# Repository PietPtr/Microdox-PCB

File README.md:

# Microdox-PCB
PCB for the Microdox keyboard.

## License

Copyright (c) 2016 Pieter Staal

This design is free software: you can redistribute it and/or modify
it under the terms of the GNU General Public License as published by
the Free Software Foundation, either version 3 of the License, or
(at your option) any later version.

This design is distributed in the hope that it will be useful,
but WITHOUT ANY WARRANTY; without even the implied warranty of
MERCHANTABILITY or FITNESS FOR A PARTICULAR PURPOSE.  See the
GNU General Public License for more details.

You should have received a copy of the GNU General Public License
along with this design.  If not, see <http://www.gnu.org/licenses/>.

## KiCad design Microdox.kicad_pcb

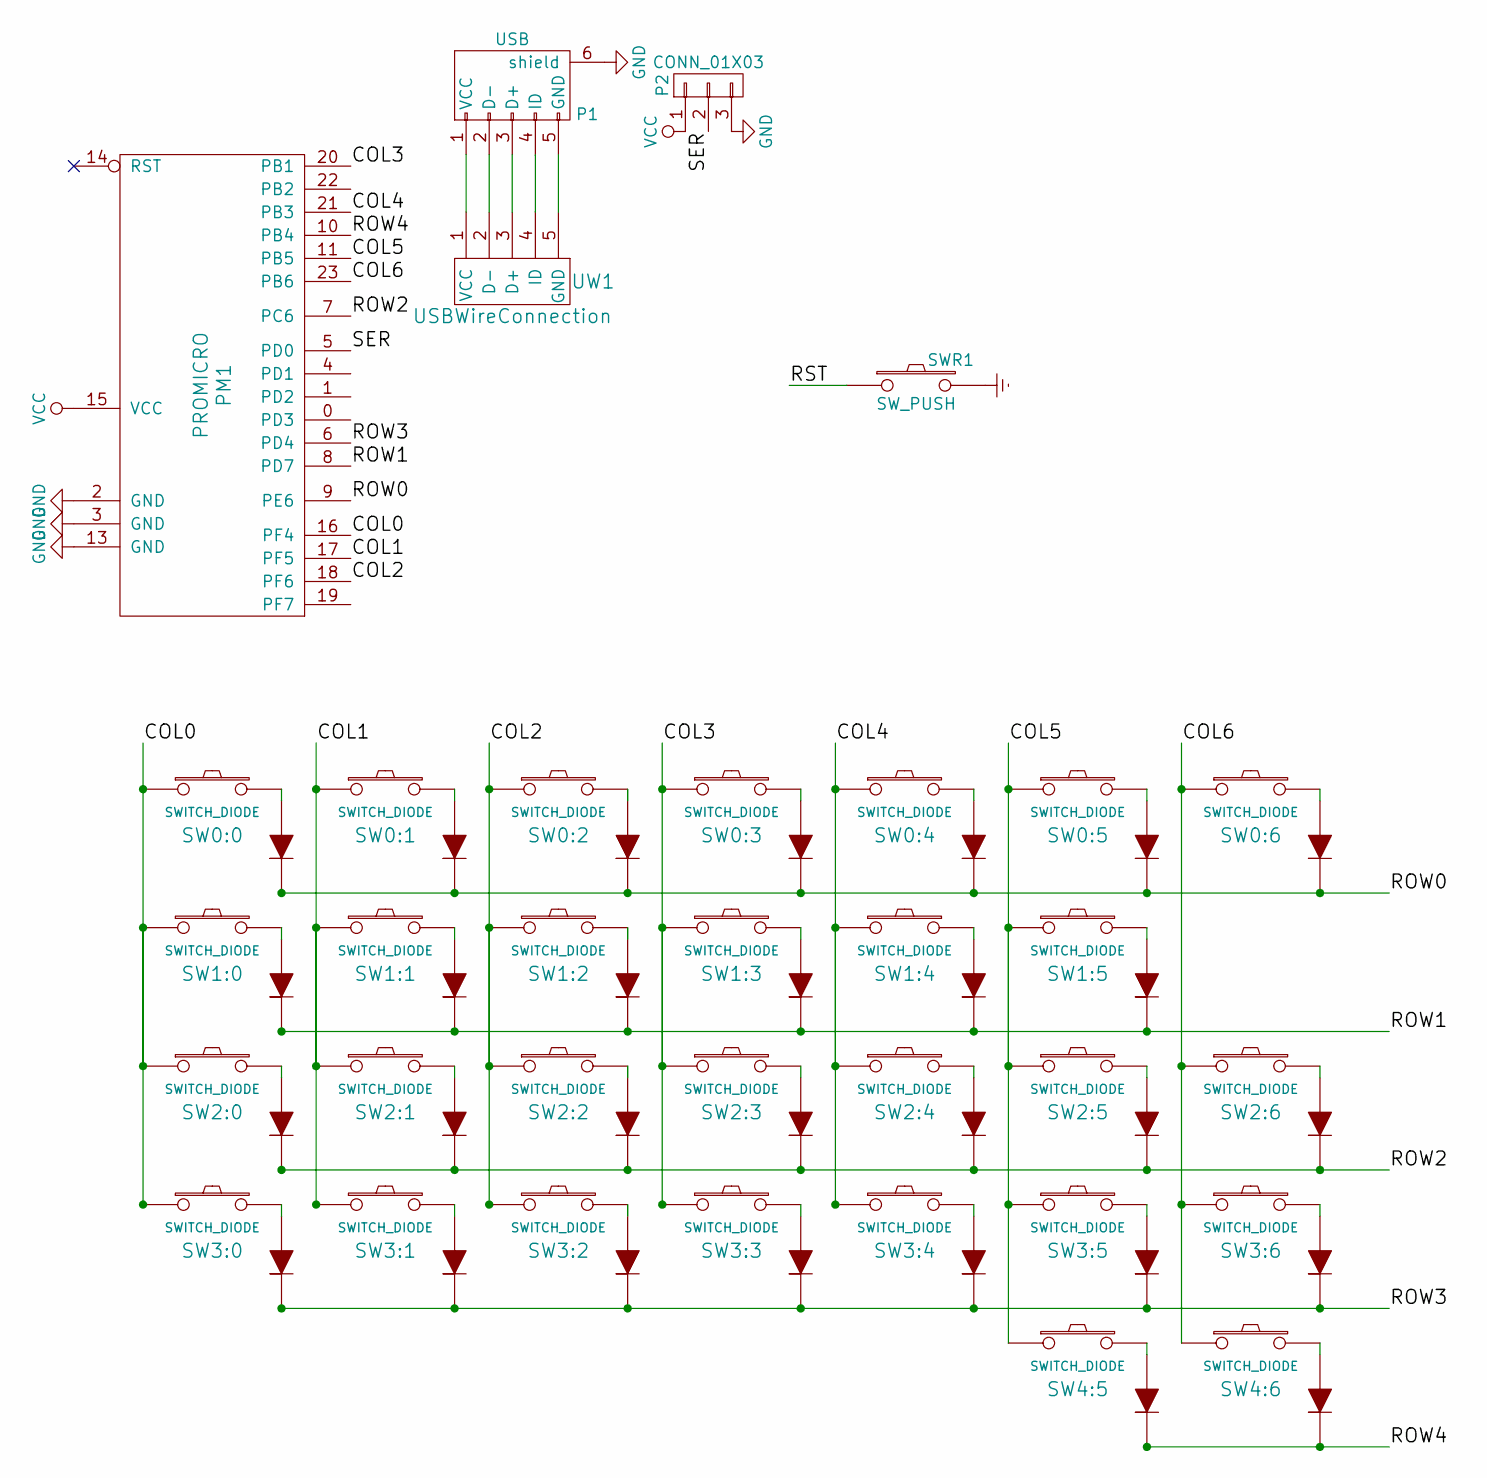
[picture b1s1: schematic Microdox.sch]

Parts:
P1: USB; USBMINI
P2: CONN_01X03; Pin_Header_Angled_1x03
PM1: PROMICRO
SW0:0, SW0:1, SW0:2, SW0:3, SW0:4, SW0:5, SW0:6, SW1:0, SW1:1, SW1:2, SW1:3, SW1:4, SW1:5, SW2:0, SW2:1, SW2:2, SW2:3, SW2:4, SW2:5, SW2:6, SW3:0, SW3:1, SW3:2, SW3:3, SW3:4, SW3:5, SW3:6, SW4:5, SW4:6: SWITCH_DIODE; MX_FLIP_DIODE
SWR1: SW_PUSH; SW_Tactile_SPST_Angled
UW1: USBWireConnection; USBWirePins

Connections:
/COL0: PM1.16 (PF4), SW0:0.1, SW1:0.1, SW2:0.1, SW3:0.1
/COL1: PM1.17 (PF5), SW0:1.1, SW1:1.1, SW2:1.1, SW3:1.1
/COL2: PM1.18 (PF6), SW0:2.1, SW1:2.1, SW2:2.1, SW3:2.1
/COL3: PM1.20 (PB1), SW0:3.1, SW1:3.1, SW2:3.1, SW3:3.1
/COL4: PM1.21 (PB3), SW0:4.1, SW1:4.1, SW2:4.1, SW3:4.1
/COL5: PM1.11 (PB5), SW0:5.1, SW1:5.1, SW2:5.1, SW3:5.1, SW4:5.1
/COL6: PM1.23 (PB6), SW0:6.1, SW2:6.1, SW3:6.1, SW4:6.1
/ROW0: PM1.9 (PE6), SW0:0.4 (K), SW0:1.4 (K), SW0:2.4 (K), SW0:3.4 (K), SW0:4.4 (K), SW0:5.4 (K), SW0:6.4 (K)
/ROW1: PM1.8 (PD7), SW1:0.4 (K), SW1:1.4 (K), SW1:2.4 (K), SW1:3.4 (K), SW1:4.4 (K), SW1:5.4 (K)
/ROW2: PM1.7 (PC6), SW2:0.4 (K), SW2:1.4 (K), SW2:2.4 (K), SW2:3.4 (K), SW2:4.4 (K), SW2:5.4 (K), SW2:6.4 (K)
/ROW3: PM1.6 (PD4), SW3:0.4 (K), SW3:1.4 (K), SW3:2.4 (K), SW3:3.4 (K), SW3:4.4 (K), SW3:5.4 (K), SW3:6.4 (K)
/ROW4: PM1.10 (PB4), SW4:5.4 (K), SW4:6.4 (K)
/SER: P2.2, PM1.5 (PD0)
GND: P1.6 (shield), P2.3, PM1.2 (GND), PM1.3 (GND), PM1.13 (GND)
unnamed: P1.1 (VCC), UW1.1 (VCC)
unnamed: P1.2 (D-), UW1.2 (D-)
unnamed: P1.3 (D+), UW1.3 (D+)
unnamed: P1.4 (ID), UW1.4 (ID)
unnamed: P1.5 (GND), UW1.5 (GND)
unnamed: SW0:0.2, SW0:0.3 (A)
unnamed: SW0:1.2, SW0:1.3 (A)
unnamed: SW0:2.2, SW0:2.3 (A)
unnamed: SW0:3.2, SW0:3.3 (A)
unnamed: SW0:4.2, SW0:4.3 (A)
unnamed: SW0:5.2, SW0:5.3 (A)
unnamed: SW0:6.2, SW0:6.3 (A)
unnamed: SW1:0.2, SW1:0.3 (A)
unnamed: SW1:1.2, SW1:1.3 (A)
unnamed: SW1:2.2, SW1:2.3 (A)
unnamed: SW1:3.2, SW1:3.3 (A)
unnamed: SW1:4.2, SW1:4.3 (A)
unnamed: SW1:5.2, SW1:5.3 (A)
unnamed: SW2:0.2, SW2:0.3 (A)
unnamed: SW2:1.2, SW2:1.3 (A)
unnamed: SW2:2.2, SW2:2.3 (A)
unnamed: SW2:3.2, SW2:3.3 (A)
unnamed: SW2:4.2, SW2:4.3 (A)
unnamed: SW2:5.2, SW2:5.3 (A)
unnamed: SW2:6.2, SW2:6.3 (A)
unnamed: SW3:0.2, SW3:0.3 (A)
unnamed: SW3:1.2, SW3:1.3 (A)
unnamed: SW3:2.2, SW3:2.3 (A)
unnamed: SW3:3.2, SW3:3.3 (A)
unnamed: SW3:4.2, SW3:4.3 (A)
unnamed: SW3:5.2, SW3:5.3 (A)
unnamed: SW3:6.2, SW3:6.3 (A)
unnamed: SW4:5.2, SW4:5.3 (A)
unnamed: SW4:6.2, SW4:6.3 (A)
VCC: P2.1, PM1.15 (VCC)

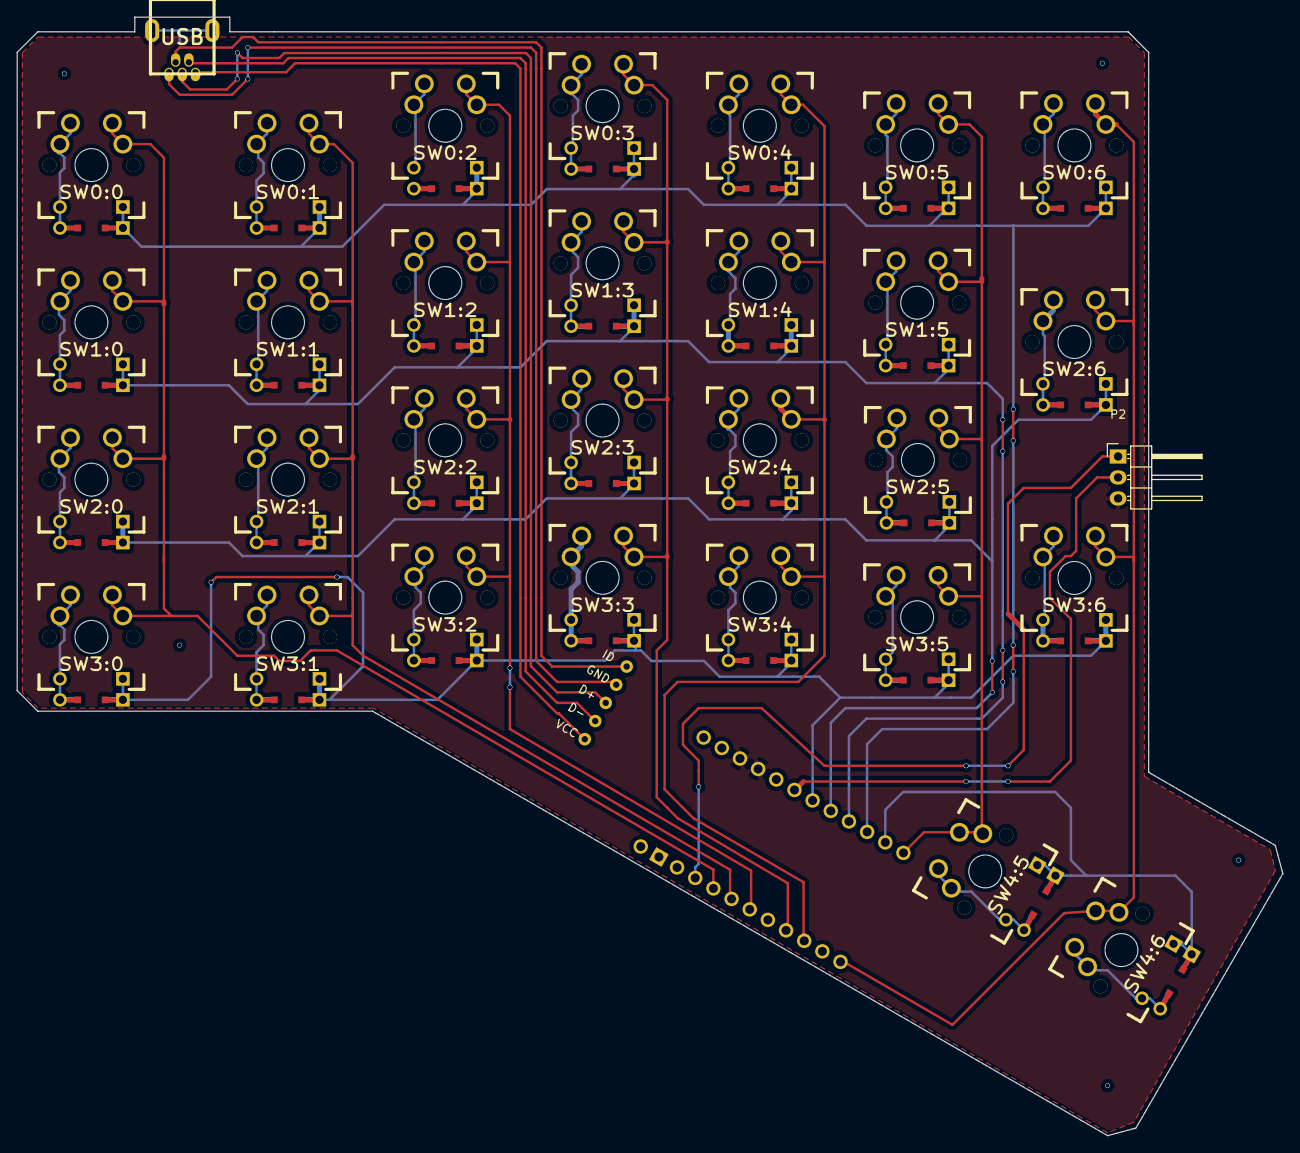
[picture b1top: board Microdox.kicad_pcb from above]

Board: 2 copper layers, 153.3 x 135.5 mm, 32 parts (1 on the bottom side), 44 nets.

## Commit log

2016-04-09 Remove png
2016-04-09 Add libs
2016-04-09 Add Readme
2016-04-11 Add license details
2016-04-11 Change license details
2016-04-11 Fix track too close to pad
2016-04-18 Made all traces 0.3mm
2016-05-07 Add version without backlighting
2016-05-08 Add gerber files
2016-05-11 Update gerber files
2016-05-11 Add more vias
    Fix non-connectivity island
2016-07-02 Add proper 3.5mm jack pins
2016-10-02 Update?
    Honestly I have no idea what I changed ._.
